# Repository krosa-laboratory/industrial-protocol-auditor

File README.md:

# industrial-protocol-auditor
Portable Hardware Implant for IT/OT Red Teaming Operations.

Features: WiFi/BLE Reconnaissance, CAN Bus Injection, Modbus MITM & Sub-GHz Signal Analysis.

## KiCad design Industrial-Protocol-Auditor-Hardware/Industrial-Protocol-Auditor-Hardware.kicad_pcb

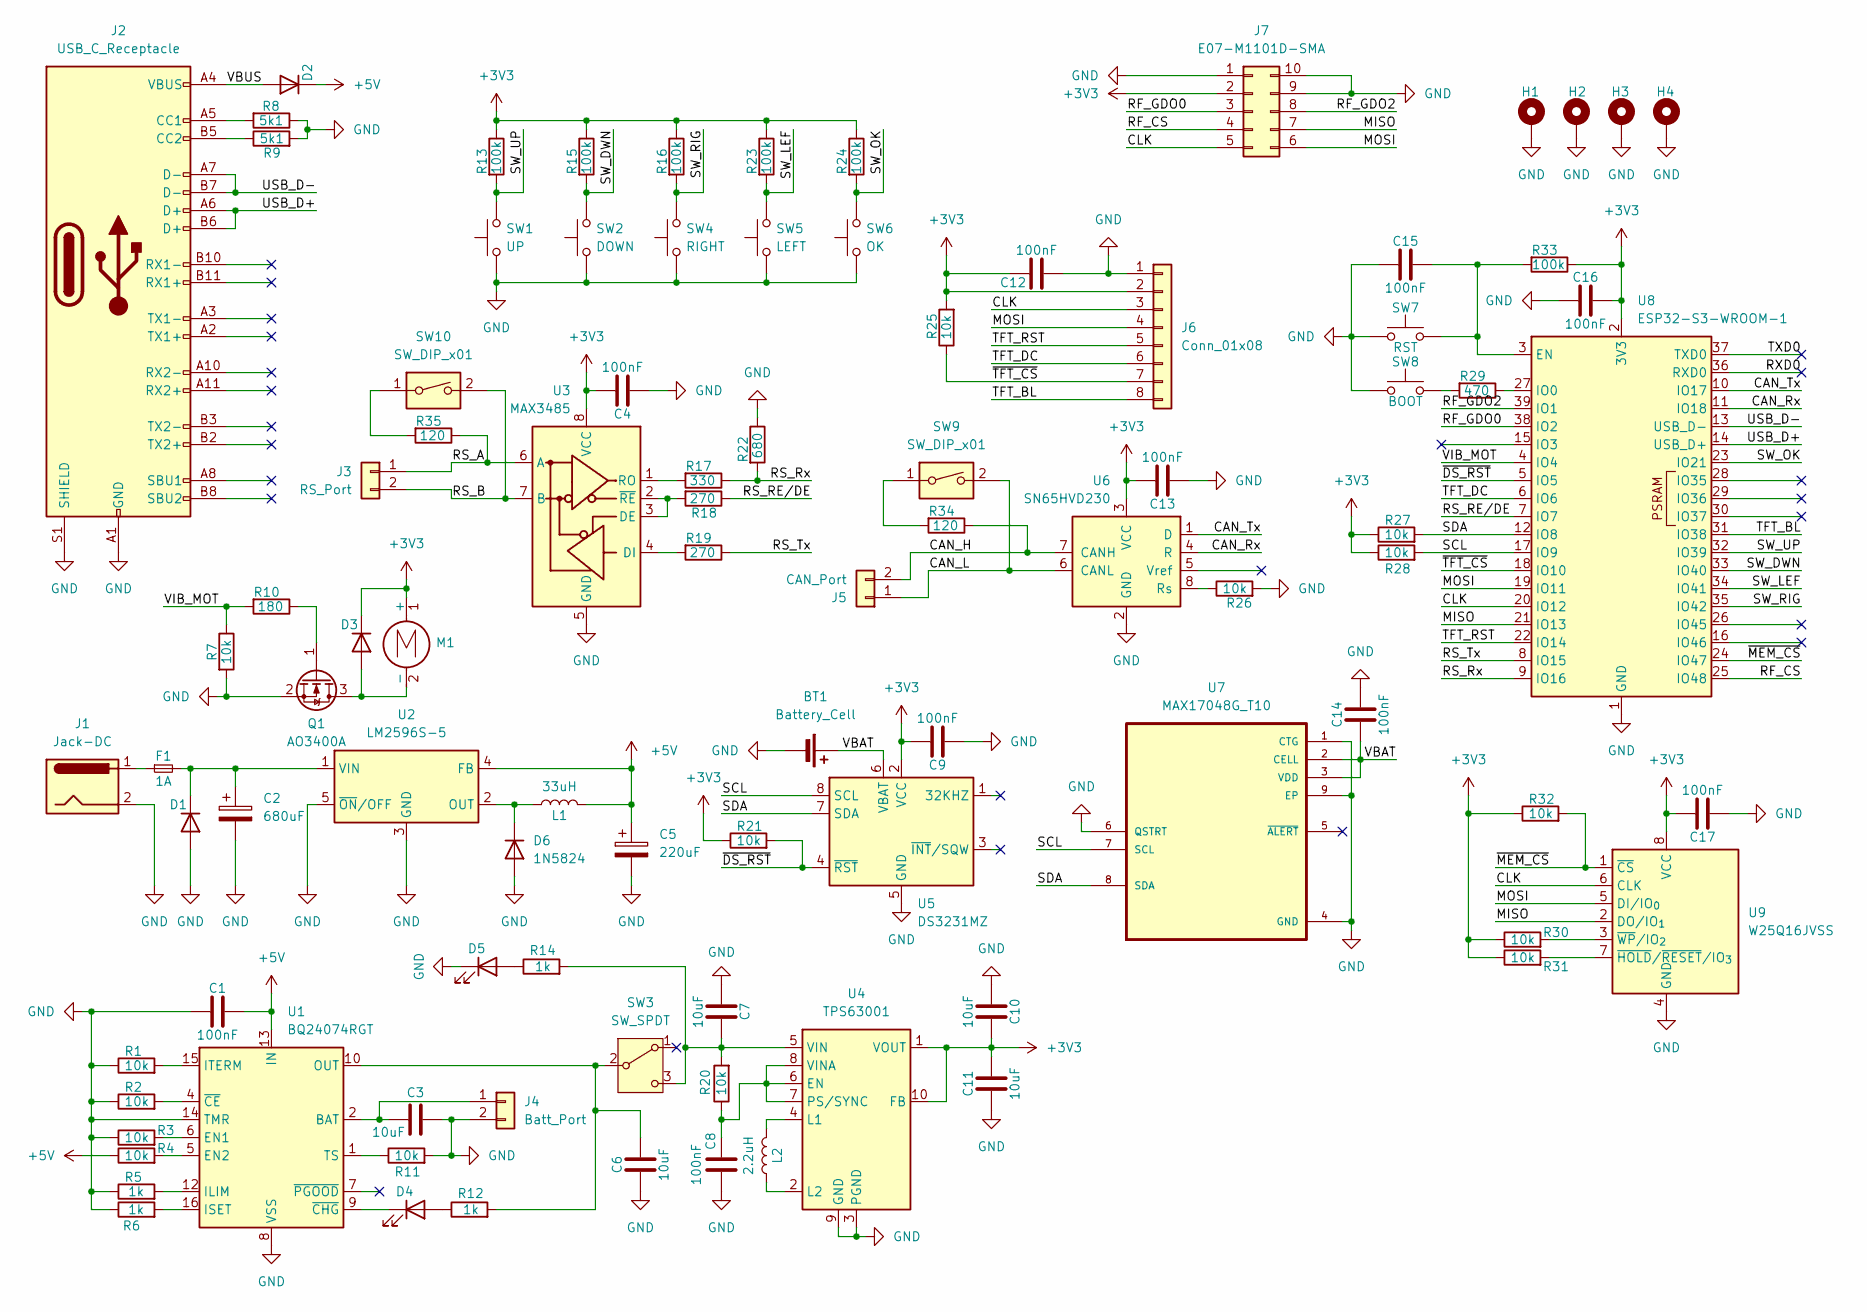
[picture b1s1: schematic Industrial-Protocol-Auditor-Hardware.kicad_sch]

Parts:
BT1: Battery_Cell; BatteryHolder_LINX_BAT-HLD-012-SMT; LCSC Part C964817
C1, C4, C8, C9, C12, C13, C14, C15, C16, C17: 100nF; C_0603_1608Metric; LCSC Part C14663
C2: 680uF; CP_Elec_10x10.5; LCSC Part C2983320
C3, C6, C7, C10, C11: 10uF; C_0603_1608Metric; LCSC Part C19702
C5: 220uF; CP_Elec_6.3x7.7; LCSC Part C2887273
D1, D2, D3, D6: 1N5824; D_SMA; LCSC Part C8678
D4, D5: LED; LED_0603_1608Metric; LCSC Part C2286
F1: 1A; Fuse_1206_3216Metric; LCSC Part C720075
H1, H2, H3, H4: MountingHole_Pad; MountingHole_2.7mm_M2.5
J1: Jack-DC; BarrelJack_Horizontal; LCSC Part C16214
J2: USB_C_Receptacle; USB_C_Receptacle_GCT_USB4105-xx-A_16P_TopMnt_Horizontal; LCSC Part C393939
J3: RS_Port; TerminalBlock_MaiXu_MX126-5.0-02P_1x02_P5.00mm; LCSC Part C474881
J4: Batt_Port; JST_XH_S2B-XH-A_1x02_P2.50mm_Horizontal; LCSC Part C157931
J5: CAN_Port; TerminalBlock_MaiXu_MX126-5.0-02P_1x02_P5.00mm; LCSC Part C474881
J6: Conn_01x08; JST_XH_S8B-XH-A_1x08_P2.50mm_Horizontal; LCSC Part C157914
J7: E07-M1101D-SMA; PinHeader_2x05_P2.54mm_Vertical
L1: 33uH; L_Chilisin_BMRF00101040; LCSC Part C6364680
L2: 2.2uH; L_1008_2520Metric; LCSC Part C86092
M1: Motor_DC; PinHeader_1x02_P2.54mm_Vertical
Q1: AO3400A; SOT-23; LCSC Part C20917
R1, R2, R3, R4, R7, R11, R20, R21, R25, R26, R27, R28, R30, R31, R32: 10k; R_0603_1608Metric; LCSC Part C25804
R5, R6, R12, R14: 1k; R_0603_1608Metric; LCSC Part C21190
R8, R9: 5k1; R_0603_1608Metric; LCSC Part C23186
R10: 180; R_0603_1608Metric; LCSC Part C2907000
R13, R15, R16, R23, R24, R33: 100k; R_0603_1608Metric; LCSC Part C25803
R17: 330; R_0603_1608Metric; LCSC Part C23138
R18, R19: 270; R_0603_1608Metric; LCSC Part C22966
R22: 680; R_0603_1608Metric; LCSC Part C23228
R29: 470; R_0603_1608Metric; LCSC Part C23179
R34, R35: 120; R_0603_1608Metric; LCSC Part C23228
SW1: UP; SW_SPST_PTS645Sx43SMTR92; LCSC Part C19191552
SW2: DOWN; SW_SPST_PTS645Sx43SMTR92; LCSC Part C19191552
SW3: SW_SPDT; SW_Slide_SPDT_Angled_CK_OS102011MA1Q; LCSC Part C431548
SW4: RIGHT; SW_SPST_PTS645Sx43SMTR92; LCSC Part C19191552
SW5: LEFT; SW_SPST_PTS645Sx43SMTR92; LCSC Part C19191552
SW6: OK; SW_SPST_PTS645Sx43SMTR92; LCSC Part C19191552
SW7: RST; SW_SPST_PTS645Sx43SMTR92; LCSC Part C19191552
SW8: BOOT; SW_SPST_PTS645Sx43SMTR92; LCSC Part C19191552
SW9, SW10: SW_DIP_x01; SW_DIP_SPSTx01_Slide_6.7x4.1mm_W6.73mm_P2.54mm_LowProfile_J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
U1: BQ24074RGT; VQFN-16-1EP_3x3mm_P0.5mm_EP1.6x1.6mm; LCSC Part C2861252
U2: LM2596S-5; TO-263-5_TabPin3; LCSC Part C347421
U3: MAX3485; SOIC-8_3.9x4.9mm_P1.27mm; LCSC Part C9943
U4: TPS63001; Texas_DRC0010J_ThermalVias; LCSC Part C28060
U5: DS3231MZ; SOIC-8_5.3x5.3mm_P1.27mm; LCSC Part C107410
U6: SN65HVD230; SOIC-8_3.9x4.9mm_P1.27mm; LCSC Part C12084
U7: MAX17048G_T10; DFN-8-1EP_2x2mm_P0.5mm_EP0.8x1.6mm; LCSC Part C2682616
U8: ESP32-S3-WROOM-1; LCSC Part C2913202
U9: W25Q16JVSS; SOIC-8_5.3x5.3mm_P1.27mm; LCSC Part C82317

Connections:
+3V3: C4.2, C9.2, C10.2, C11.2, C12.2, C13.2, C16.2, C17.2, D3.1 (K), J6.2, J7.2, M1.1 (+), R13.1, R15.1, R16.1, R21.1, R23.1, R24.1, R25.2, R27.1, R28.1, R30.1, R31.1, R32.1, R33.1, U3.8 (VCC), U4.1 (VOUT), U4.10 (FB), U5.2 (VCC), U6.3 (VCC), U8.2 (3V3), U9.8 (VCC)
+5V: C1.2, C5.1, D2.1 (K), L1.2, R4.1, U1.13 (IN), U2.4 (FB)
/CAN_H: J5.2, R34.1, U6.7 (CANH)
/CAN_L: J5.1, SW9.2, U6.6 (CANL)
/CAN_Rx: U6.4 (R), U8.11 (IO18)
/CAN_Tx: U6.1 (D), U8.10 (IO17)
/CLK: J6.3, J7.5, U8.20 (IO12), U9.6 (CLK)
/MISO: J7.7, U8.21 (IO13), U9.2 (DO/IO_{1})
/MOSI: J6.4, J7.6, U8.19 (IO11), U9.5 (DI/IO_{0})
/RF_CS: J7.4, U8.25 (IO48)
/RF_GDO0: J7.3, U8.38 (IO2)
/RF_GDO2: J7.8, U8.39 (IO1)
/RS_A: J3.1, R35.1, U3.6 (A)
/RS_B: J3.2, SW10.2, U3.7 (B)
/RS_RE/DE: R18.1, U8.7 (IO7)
/RS_Rx: R17.1, R22.2, U8.9 (IO16)
/RS_Tx: R19.1, U8.8 (IO15)
/RXD0: U8.36 (RXD0)
/SCL: R28.2, U5.8 (SCL), U7.7 (SCL), U8.17 (IO9)
/SDA: R27.2, U5.7 (SDA), U7.8 (SDA), U8.12 (IO8)
/SW_DWN: R15.2, SW2.2, U8.33 (IO40)
/SW_LEF: R23.2, SW5.2, U8.34 (IO41)
/SW_OK: R24.2, SW6.2, U8.23 (IO21)
/SW_RIG: R16.2, SW4.2, U8.35 (IO42)
/SW_UP: R13.2, SW1.2, U8.32 (IO39)
/TFT_BL: J6.8, U8.31 (IO38)
/TFT_DC: J6.6, U8.6 (IO6)
/TFT_RST: J6.5, U8.22 (IO14)
/TXD0: U8.37 (TXD0)
/USB_D+: J2.A6 (D+), J2.B6 (D+), U8.14 (USB_D+)
/USB_D-: J2.A7 (D-), J2.B7 (D-), U8.13 (USB_D-)
/VBAT: BT1.1 (+), C14.1, U5.6 (VBAT), U7.2 (CELL), U7.3 (VDD)
/VBUS: D2.2 (A), J2.A4 (VBUS), J2.A9 (VBUS), J2.B4 (VBUS), J2.B9 (VBUS)
/VIB_MOT: R7.1, R10.2, U8.4 (IO4)
/~DS_RST: R21.2, U5.4 (~RST), U8.5 (IO5)
/~MEM_CS: R32.2, U8.24 (IO47), U9.1 (~CS)
/~TFT_CS: J6.7, R25.1, U8.18 (IO10)
GND: BT1.2 (-), C1.1, C2.2, C3.2, C4.1, C5.2, C6.1, C7.1, C8.1, C9.1, C10.1, C11.1, C12.1, C13.1, C14.2, C15.1, C16.1, C17.1, D1.2 (A), D5.1 (K), D6.2 (A), H1.1, H2.1, H3.1, H4.1, J1.2, J2.A1 (GND), J2.A12 (GND), J2.B1 (GND), J2.B12 (GND), J2.S1 (SHIELD), J4.2, J6.1, J7.1, J7.9, J7.10, Q1.2 (S), R1.1, R2.1, R3.1, R5.1, R6.1, R7.2, R8.1, R9.2, R11.2, R22.1, R26.2, SW1.1, SW2.1, SW4.1, SW5.1, SW6.1, SW7.1, SW8.1, U1.8 (VSS), U1.14 (TMR), U1.17 (VSS), U2.3 (GND), U2.5 (~ON/OFF), U3.5 (GND), U4.3 (PGND), U4.9 (GND), U4.11 (PGND), U5.5 (GND), U6.2 (GND), U7.1 (CTG), U7.4 (GND), U7.6 (QSTRT), U7.9 (EP), U8.1 (GND), U8.40 (GND), U8.41 (GND), U9.4 (GND)
unnamed: C2.1, D1.1 (K), F1.2, U2.1 (VIN)
unnamed: D3.2 (A), M1.2 (-), Q1.3 (D)
unnamed: D4.2 (A), R12.1
unnamed: D4.1 (K), U1.9 (~CHG)
unnamed: D5.2 (A), R14.1
unnamed: D6.1 (K), L1.1, U2.2 (OUT)
unnamed: F1.1, J1.1
unnamed: J2.A5 (CC1), R8.2
unnamed: J2.B5 (CC2), R9.1
unnamed: C3.1, J4.1, U1.2 (BAT), U1.3 (BAT)
unnamed: Q1.1 (G), R10.1
unnamed: R29.2, SW8.2
unnamed: R34.2, SW9.1
unnamed: R35.2, SW10.1
unnamed: C6.2, R12.2, SW3.2 (B), U1.10 (OUT), U1.11 (OUT)
unnamed: C7.2, R14.2, R20.2, SW3.3 (C), U4.5 (VIN)
unnamed: R3.2, U1.6 (EN1)
unnamed: R4.2, U1.5 (EN2)
unnamed: R5.2, U1.12 (ILIM)
unnamed: R6.2, U1.16 (ISET)
unnamed: R1.2, U1.15 (ITERM)
unnamed: R11.1, U1.1 (TS)
unnamed: R2.2, U1.4 (~CE)
unnamed: R18.2, U3.2 (~RE), U3.3 (DE)
unnamed: R19.2, U3.4 (DI)
unnamed: R17.2, U3.1 (RO)
unnamed: C8.2, R20.1, U4.6 (EN), U4.7 (PS/SYNC), U4.8 (VINA)
unnamed: L2.2, U4.4 (L1)
unnamed: L2.1, U4.2 (L2)
unnamed: R26.1, U6.8 (Rs)
unnamed: C15.2, R33.2, SW7.2, U8.3 (EN)
unnamed: R29.1, U8.27 (IO0)
unnamed: R31.2, U9.7 (~HOLD/~RESET/IO_{3})
unnamed: R30.2, U9.3 (~WP/IO_{2})

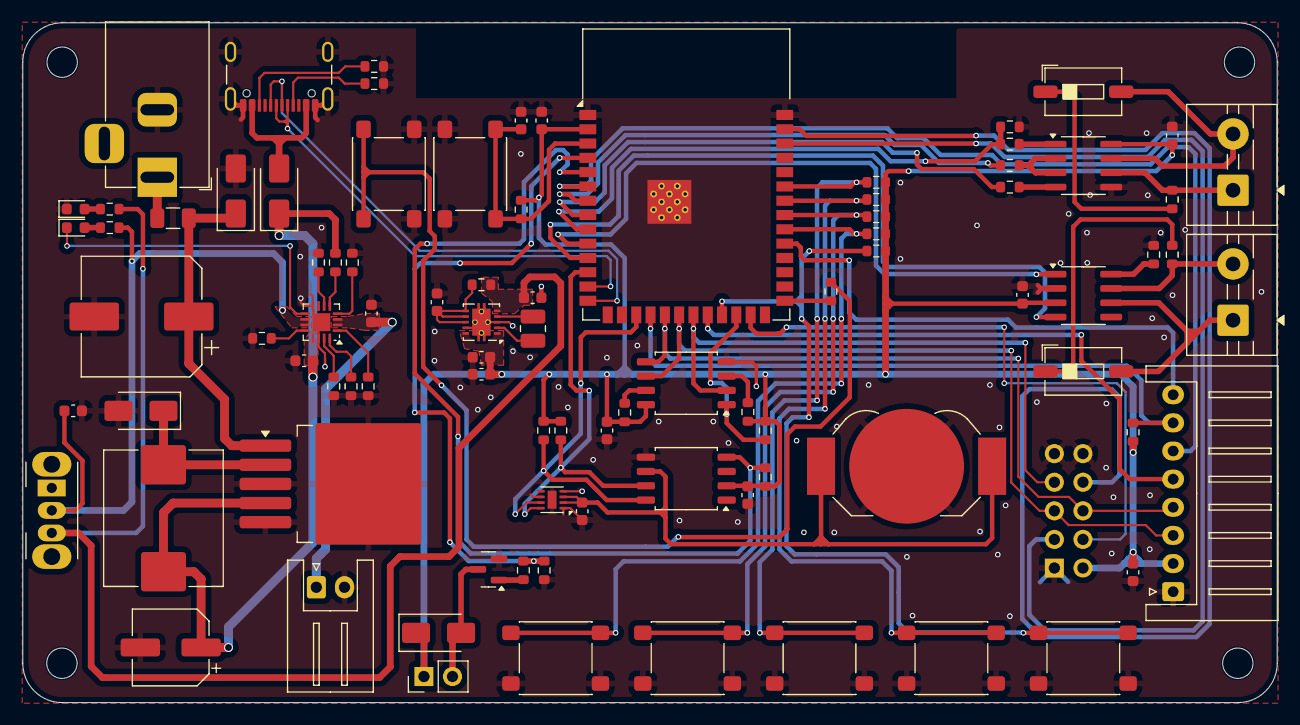
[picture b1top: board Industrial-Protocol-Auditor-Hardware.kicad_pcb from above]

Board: 2 copper layers, 111.5 x 60.4 mm, 94 parts (1 on the bottom side), 70 nets.

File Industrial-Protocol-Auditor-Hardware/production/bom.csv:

Designator,Footprint,Quantity,Value,LCSC Part #
BT1,BatteryHolder_LINX_BAT-HLD-012-SMT,1,Battery_Cell,C964817
"C1, C12, C13, C14, C15, C16, C17, C4, C8, C9",0603,10,100nF,C14663
"C10, C11, C3, C6, C7",0603,5,10uF,C19702
C2,CP_Elec_10x10.5,1,680uF,C2983320
C5,CP_Elec_6.3x7.7,1,220uF,C2887273
"D1, D2, D3, D6",D_SMA,4,1N5824,C8678
"D4, D5",0603,2,LED,C2286
F1,1206,1,1A,C720075
J1,BarrelJack_Horizontal,1,Jack-DC,C16214
J2,USB_C_Receptacle_GCT_USB4105-xx-A_16P_TopMnt_Horizontal,1,USB_C_Receptacle,C393939
J3,TerminalBlock_MaiXu_MX126-5.0-02P_1x02_P5.00mm,1,RS_Port,C474881
J4,JST_XH_S2B-XH-A_1x02_P2.50mm_Horizontal,1,Batt_Port,C157931
J5,TerminalBlock_MaiXu_MX126-5.0-02P_1x02_P5.00mm,1,CAN_Port,C474881
J6,JST_XH_S8B-XH-A_1x08_P2.50mm_Horizontal,1,Conn_01x08,C157914
J7,PinHeader_2x05_P2.54mm_Vertical,1,E07-M1101D-SMA,-
L1,L_Chilisin_BMRF00101040,1,33uH,C6364680
L2,1008,1,2.2uH,C86092
M1,PinHeader_1x02_P2.54mm_Vertical,1,Motor_DC,-
Q1,SOT-23,1,AO3400A,C20917
"R1, R11, R2, R20, R21, R25, R26, R27, R28, R3, R30, R31, R32, R4, R7",0603,15,10k,C25804
R10,0603,1,180,C2907000
"R12, R14, R5, R6",0603,4,1k,C21190
"R13, R15, R16, R23, R24, R33",0603,6,100k,C25803
R17,0603,1,330,C23138
"R18, R19",0603,2,270,C22966
R22,0603,1,680,C23228
R29,0603,1,470,C23179
"R34, R35",0603,2,120,C23228
"R8, R9",0603,2,5k1,C23186
SW1,SW_SPST_PTS645Sx43SMTR92,1,UP,C19191552
"SW10, SW9",SW_DIP_SPSTx01_Slide_6.7x4.1mm_W6.73mm_P2.54mm_LowProfile_JPin,2,SW_DIP_x01,
SW2,SW_SPST_PTS645Sx43SMTR92,1,DOWN,C19191552
SW3,SW_Slide_SPDT_Angled_CK_OS102011MA1Q,1,SW_SPDT,C431548
SW4,SW_SPST_PTS645Sx43SMTR92,1,RIGHT,C19191552
SW5,SW_SPST_PTS645Sx43SMTR92,1,LEFT,C19191552
SW6,SW_SPST_PTS645Sx43SMTR92,1,OK,C19191552
SW7,SW_SPST_PTS645Sx43SMTR92,1,RST,C19191552
SW8,SW_SPST_PTS645Sx43SMTR92,1,BOOT,C19191552
U1,VQFN-16-1EP_3x3mm_P0.5mm_EP1.6x1.6mm,1,BQ24074RGT,C2861252
U2,TO-263-5_TabPin3,1,LM2596S-5,C347421
U3,SOIC-8_3.9x4.9mm_P1.27mm,1,MAX3485,C9943
U4,Texas_DRC0010J_ThermalVias,1,TPS63001,C28060
U5,SOIC-8_5.3x5.3mm_P1.27mm,1,DS3231MZ,C107410
U6,SOIC-8_3.9x4.9mm_P1.27mm,1,SN65HVD230,C12084
U7,DFN-8-1EP_2x2mm_P0.5mm_EP0.8x1.6mm,1,MAX17048G_T10,C2682616
U8,ESP32-S3-WROOM-1,1,ESP32-S3-WROOM-1,C2913202
U9,SOIC-8_5.3x5.3mm_P1.27mm,1,W25Q16JVSS,C82317

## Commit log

2025-11-25 Add GitHub Actions workflow to add issues to project
2025-11-29 Initialized the PlatformIO project for the software works
2025-11-29 Created the KiCAD project and started the schematic. It need to be completed with RF module and the Fuel Gauge IC symbols.
2025-12-01 Populated all footprints and Component LCSC Reference. Started the board design.
2025-12-02 Finished the PCB design and created production files to get a price in JLCPCB webpage.
2025-12-05 Created a second version of the elecronics boards with lower dimensions.
2025-12-05 Created a power analysis into "power_budget.md" with worst cases of power consumption and battery autonomies.
2025-12-10 Created the STEP file for the second version of the PCB.
2025-12-10 Created file with hardware interconnection inside the board designed.
